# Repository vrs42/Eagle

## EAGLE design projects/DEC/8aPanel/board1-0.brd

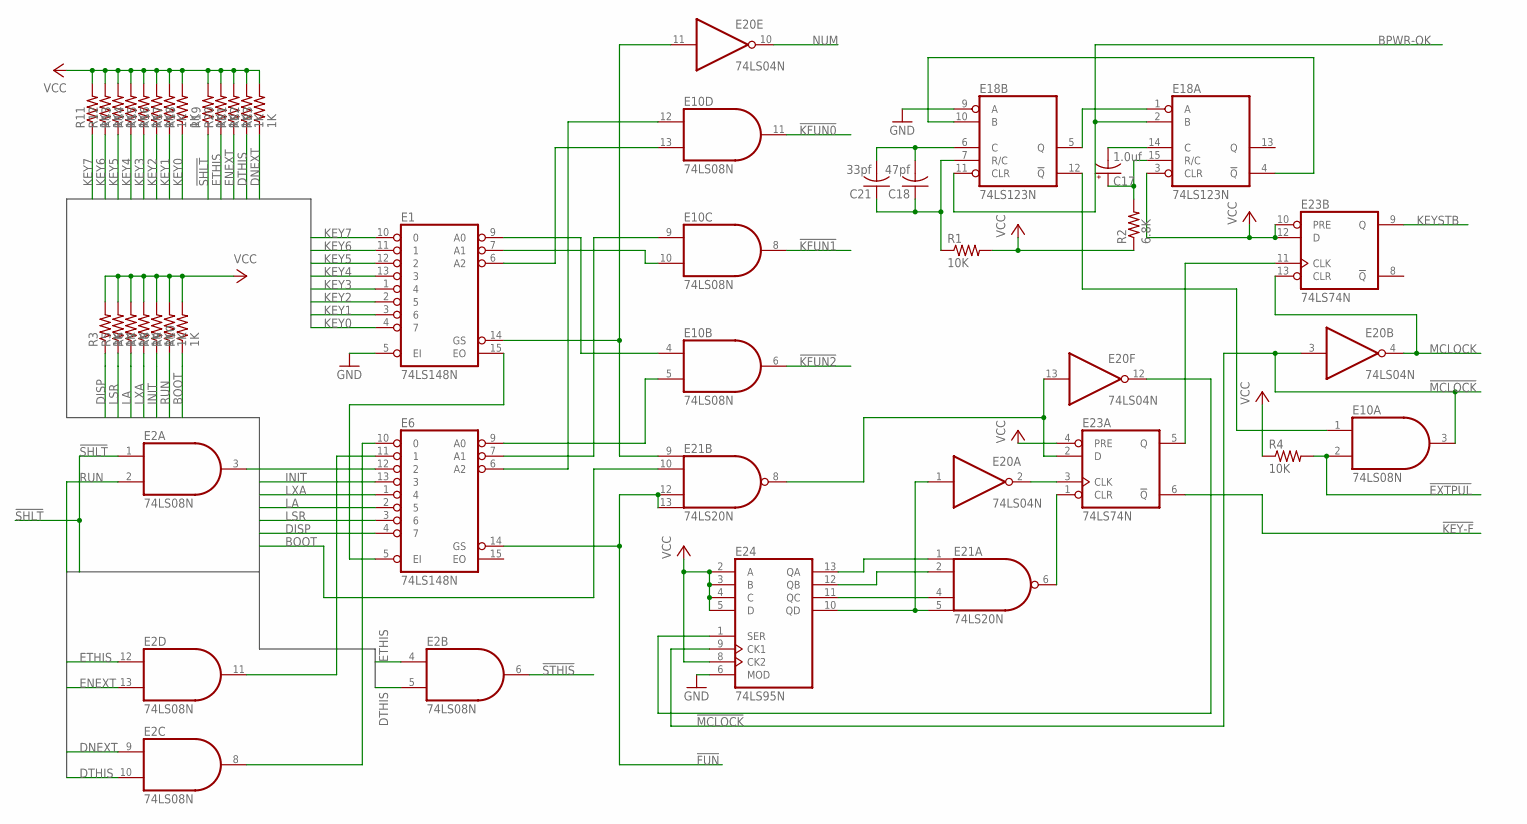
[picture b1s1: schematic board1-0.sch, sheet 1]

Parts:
C17: 1.0uf; E15-5
C18: 47pf; C050-025X075
C21: 33pf; C050-025X075
E1, E6: 74LS148N; DIL16
E2, E10: 74LS08N; DIL14
E18: 74LS123N; DIL16
E20: 74LS04N; DIL14
E21: 74LS20N; DIL14
E23: 74LS74N; DIL14
E24: 74LS95N; DIL14
R1, R4: 10K; 0207/10
R2: 6.8K; 0207/10
R3, R5, R6, R7, R8, R9, R10, R11, R12, R13, R14, R15, R16, R17, R18, R19, R20, R21, R22, R23: 1K; 0207/10

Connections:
!EXTPUL: E10.2 (I1), R4.2; also elsewhere on the board
!FUN: E6.14 (GS), E21.12 (I2), E21.13 (I3); also elsewhere on the board
!KEY-F: E23.6 (!Q); also elsewhere on the board
!KFUN0: E10.11 (O); also elsewhere on the board
!KFUN1: E10.8 (O); also elsewhere on the board
!KFUN2: E10.6 (O); also elsewhere on the board
!MCLOCK: E10.3 (O), E20.3 (I), E24.9 (CK1); also elsewhere on the board
!SHLT: E2.1 (I0), R19.1; also elsewhere on the board
!STHIS: E2.6 (O); also elsewhere on the board
BOOT: E21.10 (I1), R10.1; also elsewhere on the board
BPWR-OK: E18.2 (B), E18.11 (CLR); also elsewhere on the board
DISP: E6.4 (7), R3.1; also elsewhere on the board
DNEXT: E2.9 (I0), R23.1; also elsewhere on the board
DTHIS: E2.5 (I1), E2.10 (I1), R22.1; also elsewhere on the board
ENEXT: E2.13 (I1), R21.1; also elsewhere on the board
ETHIS: E2.4 (I0), E2.12 (I0), R20.1; also elsewhere on the board
GND: E1.5 (EI), E1.8 (GND), E2.7 (GND), E6.8 (GND), E10.7 (GND), E18.8 (GND), E18.9 (A), E20.7 (GND), E21.7 (GND), E23.7 (GND), E24.6 (MOD), E24.7 (GND); also elsewhere on the board
INIT: E6.13 (3), R8.1; also elsewhere on the board
KEY0: E1.4 (7), R18.1; also elsewhere on the board
KEY1: E1.3 (6), R17.1; also elsewhere on the board
KEY2: E1.2 (5), R16.1; also elsewhere on the board
KEY3: E1.1 (4), R15.1; also elsewhere on the board
KEY4: E1.13 (3), R14.1; also elsewhere on the board
KEY5: E1.12 (2), R13.1; also elsewhere on the board
KEY6: E1.11 (1), R12.1; also elsewhere on the board
KEY7: E1.10 (0), R11.1; also elsewhere on the board
KEYSTB: E23.9 (Q); also elsewhere on the board
LA: E6.2 (5), R6.1; also elsewhere on the board
LSR: E6.3 (6), R5.1; also elsewhere on the board
LXA: E6.1 (4), R7.1; also elsewhere on the board
MCLOCK: E20.4 (O), E23.13 (CLR); also elsewhere on the board
unnamed: E1.6 (A2), E10.13 (I1)
unnamed: E1.7 (A1), E10.10 (I1)
unnamed: E1.9 (A0), E10.4 (I0)
unnamed: E1.14 (GS), E20.11 (I), E21.9 (I0)
unnamed: E6.6 (A2), E10.12 (I0)
unnamed: E6.7 (A1), E10.9 (I0)
unnamed: E6.9 (A0), E10.5 (I1)
unnamed: E1.15 (EO), E6.5 (EI)
unnamed: E21.1 (I0), E24.13 (QA)
unnamed: E21.2 (I1), E24.12 (QB)
unnamed: E21.4 (I2), E24.11 (QC)
unnamed: E20.1 (I), E21.5 (I3), E24.10 (QD)
unnamed: E21.6 (O), E23.1 (CLR)
unnamed: E20.2 (O), E23.3 (CLK)
unnamed: E20.13 (I), E21.8 (O), E23.2 (D)
unnamed: E20.12 (O), E24.1 (SER)
unnamed: E23.5 (Q), E23.11 (CLK)
unnamed: E18.1 (A), E18.5 (Q)
unnamed: C18.1, C21.1, E18.7 (R/C), R1.1
unnamed: C17.+, E18.15 (R/C), R2.2
unnamed: C18.2, C21.2, E18.6 (C)
unnamed: C17.-, E18.14 (C)
unnamed: E2.3 (O), E6.12 (2)
unnamed: E18.4 (!Q), E18.10 (B)
unnamed: E2.11 (O), E6.11 (1)
unnamed: E2.8 (O), E6.10 (0)
unnamed: E10.1 (I0), E18.12 (!Q)
NUM: E20.10 (O); also elsewhere on the board
RUN: E2.2 (I1), R9.1; also elsewhere on the board
VCC: E1.16 (VCC), E2.14 (VCC), E6.16 (VCC), E10.14 (VCC), E18.3 (CLR), E18.16 (VCC), E20.14 (VCC), E21.14 (VCC), E23.4 (PRE), E23.10 (PRE), E23.12 (D), E23.14 (VCC), E24.2 (A), E24.3 (B), E24.4 (C), E24.5 (D), E24.8 (CK2), E24.14 (VCC), R1.2, R2.1, R3.2, R4.1, R5.2, R6.2, R7.2, R8.2, R9.2, R10.2, R11.2, R12.2, R13.2, R14.2, R15.2, R16.2, R17.2, R18.2, R19.2, R20.2, R21.2, R22.2, R23.2; also elsewhere on the board

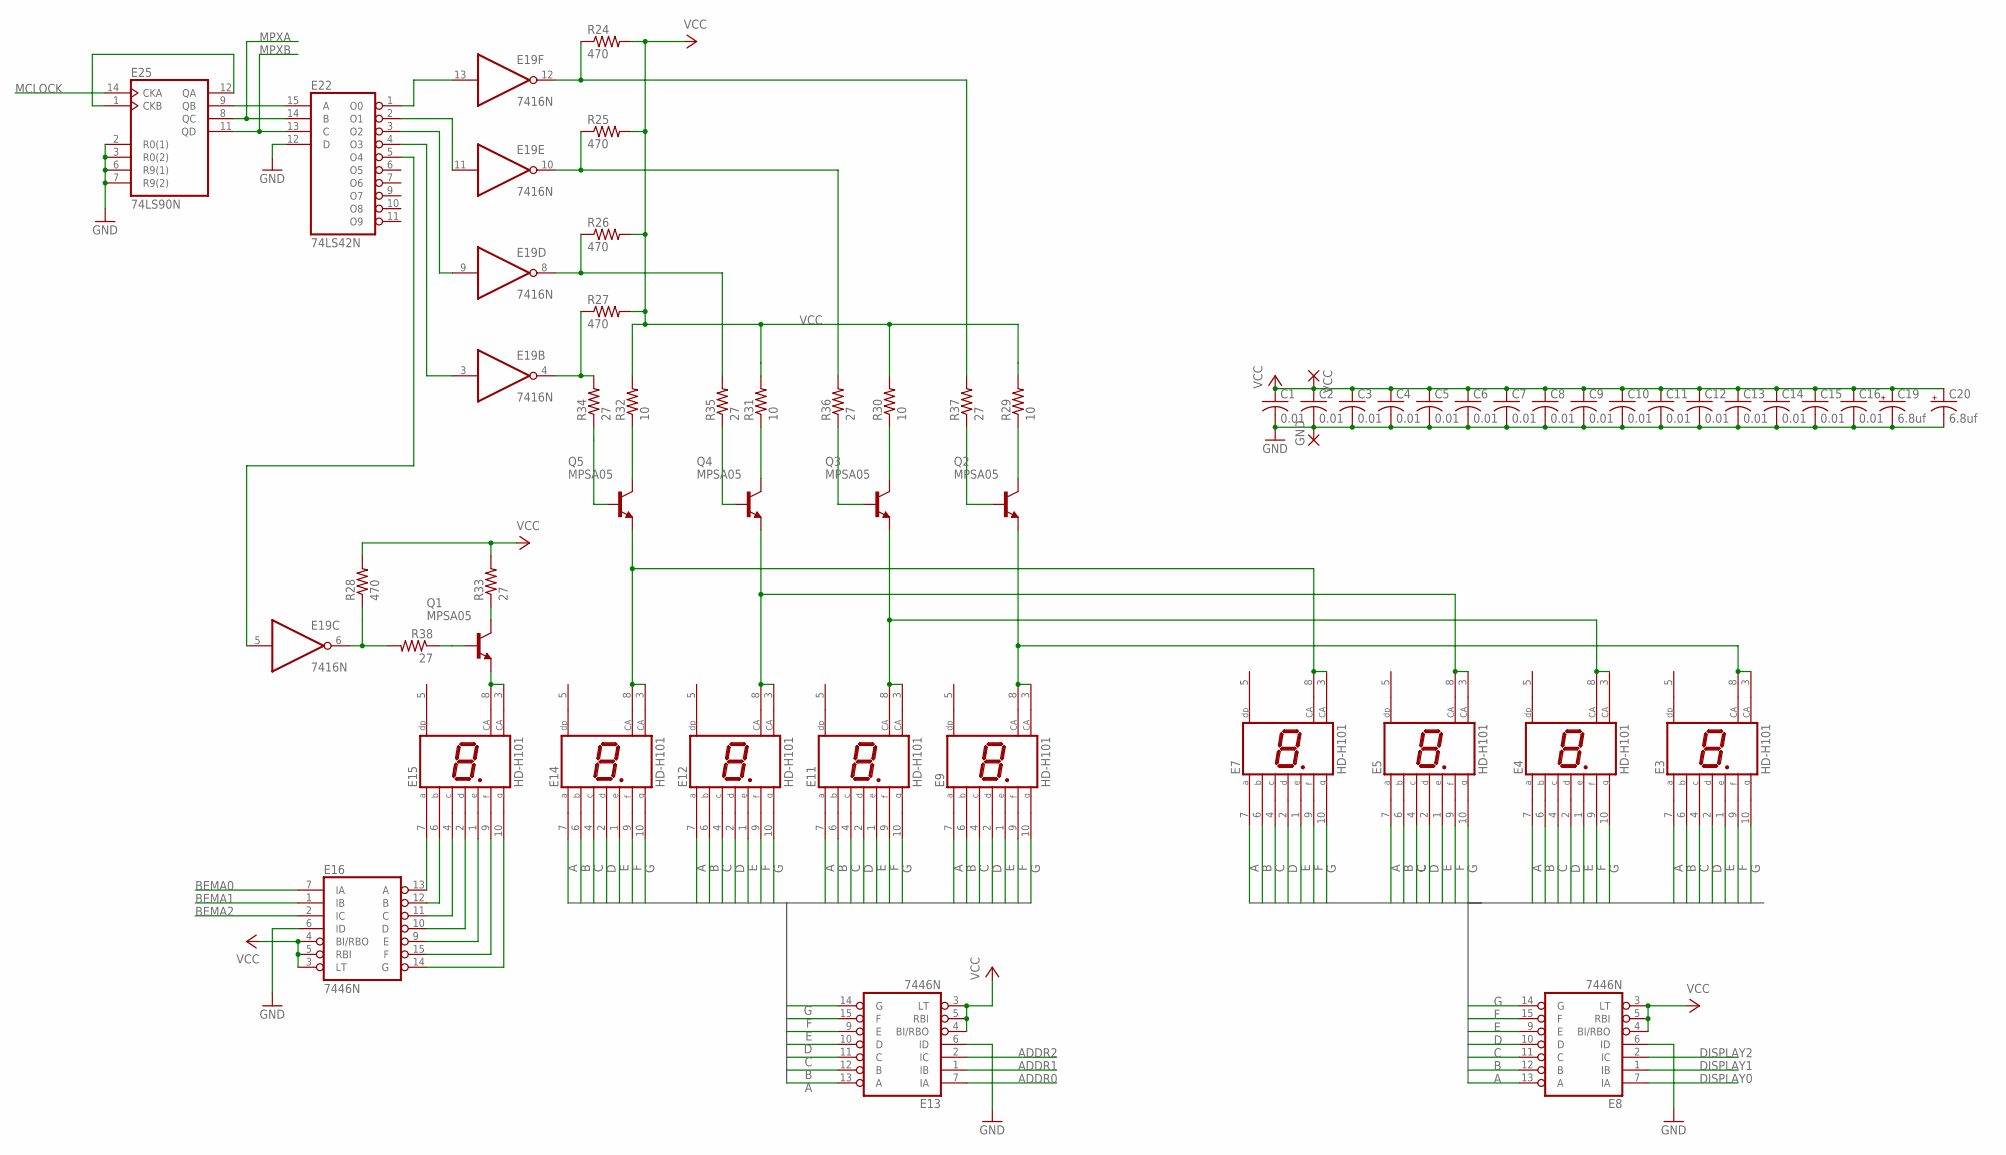
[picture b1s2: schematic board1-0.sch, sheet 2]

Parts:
C1, C2, C3, C4, C5, C6, C7, C8, C9, C10, C11, C12, C13, C14, C15, C16: 0.01; C050-025X075
C19, C20: 6.8uf; E22-6
E3, E4, E5, E7, E9, E11, E12, E14, E15: HD-H101; HDSP-M
E8, E13, E16: 7446N; DIL16
E19: 7416N; DIL14
E22: 74LS42N; DIL16
E25: 74LS90N; DIL14
GND: 3,81/1,4
Q1, Q2, Q3, Q4, Q5: MPSA05; TO18
R24, R25, R26, R27, R28: 470; 0207/10
R29, R30, R31, R32: 10; 0207/10
R33, R34, R35, R36, R37, R38: 27; 0207/10
VCC: 3,81/1,4

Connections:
A: E3.7 (A), E4.7 (A), E5.7 (A), E7.7 (A), E8.13 (A), E9.7 (A), E11.7 (A), E12.7 (A), E13.13 (A), E14.7 (A)
ADDR0: E13.7 (IA); also elsewhere on the board
ADDR1: E13.1 (IB); also elsewhere on the board
ADDR2: E13.2 (IC); also elsewhere on the board
B: E3.6 (B), E4.6 (B), E5.6 (B), E7.6 (B), E8.12 (B), E9.6 (B), E11.6 (B), E12.6 (B), E13.12 (B), E14.6 (B)
BEMA0: E16.7 (IA); also elsewhere on the board
BEMA1: E16.1 (IB); also elsewhere on the board
BEMA2: E16.2 (IC); also elsewhere on the board
C: E3.4 (C), E4.4 (C), E5.4 (C), E7.4 (C), E8.11 (C), E9.4 (C), E11.4 (C), E12.4 (C), E13.11 (C), E14.4 (C)
D: E3.2 (D), E4.2 (D), E5.2 (D), E7.2 (D), E8.10 (D), E9.2 (D), E11.2 (D), E12.2 (D), E13.10 (D), E14.2 (D)
DISPLAY0: E8.7 (IA); also elsewhere on the board
DISPLAY1: E8.1 (IB); also elsewhere on the board
DISPLAY2: E8.2 (IC); also elsewhere on the board
E: E3.1 (E), E4.1 (E), E5.1 (E), E7.1 (E), E8.9 (E), E9.1 (E), E11.1 (E), E12.1 (E), E13.9 (E), E14.1 (E)
F: E3.9 (F), E4.9 (F), E5.9 (F), E7.9 (F), E8.15 (F), E9.9 (F), E11.9 (F), E12.9 (F), E13.15 (F), E14.9 (F)
G: E3.10 (G), E4.10 (G), E5.10 (G), E7.10 (G), E8.14 (G), E9.10 (G), E11.10 (G), E12.10 (G), E13.14 (G), E14.10 (G)
GND: C1.2, C2.2, C3.2, C4.2, C5.2, C6.2, C7.2, C8.2, C9.2, C10.2, C11.2, C12.2, C13.2, C14.2, C15.2, C16.2, C19.-, C20.-, E8.6 (ID), E8.8 (GND), E13.6 (ID), E13.8 (GND), E16.6 (ID), E16.8 (GND), E19.7 (GND), E22.8 (GND), E22.12 (D), E25.2 (R0(1)), E25.3 (R0(2)), E25.6 (R9(1)), E25.7 (R9(2)), E25.10 (GND), GND.1; also elsewhere on the board
MCLOCK: E25.14 (CKA); also elsewhere on the board
MPXA: E22.14 (B), E25.8 (QC); also elsewhere on the board
MPXB: E22.13 (C), E25.11 (QD); also elsewhere on the board
unnamed: E15.7 (A), E16.13 (A)
unnamed: E15.6 (B), E16.12 (B)
unnamed: E15.4 (C), E16.11 (C)
unnamed: E15.2 (D), E16.10 (D)
unnamed: E15.1 (E), E16.9 (E)
unnamed: E15.9 (F), E16.15 (F)
unnamed: E15.10 (G), E16.14 (G)
unnamed: E19.12 (O), R24.1, R37.2
unnamed: E19.10 (O), R25.1, R36.2
unnamed: E22.15 (A), E25.9 (QB)
unnamed: E25.1 (CKB), E25.12 (QA)
unnamed: E19.8 (O), R26.1, R35.2
unnamed: E19.13 (I), E22.1 (O0)
unnamed: E19.11 (I), E22.2 (O1)
unnamed: E19.9 (I), E22.3 (O2)
unnamed: E19.3 (I), E22.4 (O3)
unnamed: E19.5 (I), E22.5 (O4)
unnamed: E19.4 (O), R27.1, R34.2
unnamed: E15.3 (CA), E15.8 (CA), Q1.1 (E)
unnamed: Q2.3 (C), R29.1
unnamed: Q3.3 (C), R30.1
unnamed: Q4.3 (C), R31.1
unnamed: Q5.3 (C), R32.1
unnamed: Q1.3 (C), R33.1
unnamed: Q1.2 (B), R38.1
unnamed: E7.3 (CA), E7.8 (CA), E14.3 (CA), E14.8 (CA), Q5.1 (E)
unnamed: Q5.2 (B), R34.1
unnamed: Q4.2 (B), R35.1
unnamed: Q3.2 (B), R36.1
unnamed: Q2.2 (B), R37.1
unnamed: E19.6 (O), R28.1, R38.2
unnamed: E5.3 (CA), E5.8 (CA), E12.3 (CA), E12.8 (CA), Q4.1 (E)
unnamed: E4.3 (CA), E4.8 (CA), E11.3 (CA), E11.8 (CA), Q3.1 (E)
unnamed: E3.3 (CA), E3.8 (CA), E9.3 (CA), E9.8 (CA), Q2.1 (E)
VCC: C1.1, C2.1, C3.1, C4.1, C5.1, C6.1, C7.1, C8.1, C9.1, C10.1, C11.1, C12.1, C13.1, C14.1, C15.1, C16.1, C19.+, C20.+, E8.3 (LT), E8.4 (BI/RBO), E8.5 (RBI), E8.16 (VCC), E13.3 (LT), E13.4 (BI/RBO), E13.5 (RBI), E13.16 (VCC), E16.3 (LT), E16.4 (BI/RBO), E16.5 (RBI), E16.16 (VCC), E19.14 (VCC), E22.16 (VCC), E25.5 (VCC), R24.2, R25.2, R26.2, R27.2, R28.2, R29.2, R30.2, R31.2, R32.2, R33.2, VCC.1; also elsewhere on the board

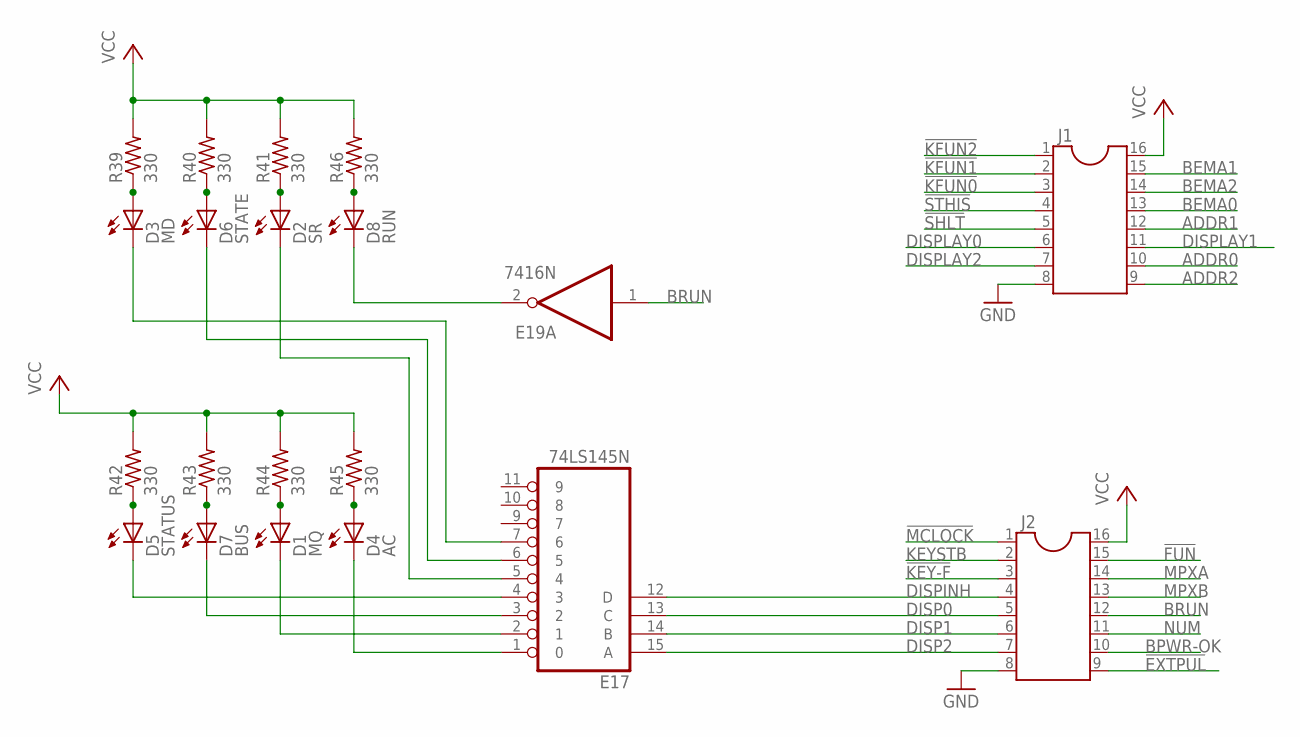
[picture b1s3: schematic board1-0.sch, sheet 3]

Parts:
D1: MQ; LED5MM
D2: SR; LED5MM
D3: MD; LED5MM
D4: AC; LED5MM
D5: STATUS; LED5MM
D6: STATE; LED5MM
D7: BUS; LED5MM
D8: RUN; LED5MM
E17: 74LS145N; DIL16
E19: 7416N; DIL14
J1, J2: DIL16S; SOCKET-16
R39, R40, R41, R42, R43, R44, R45, R46: 330; 0207/10

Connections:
!EXTPUL: J2.9; also elsewhere on the board
!FUN: J2.15; also elsewhere on the board
!KEY-F: J2.3; also elsewhere on the board
!KFUN0: J1.3; also elsewhere on the board
!KFUN1: J1.2; also elsewhere on the board
!KFUN2: J1.1; also elsewhere on the board
!MCLOCK: J2.1; also elsewhere on the board
!SHLT: J1.5; also elsewhere on the board
!STHIS: J1.4; also elsewhere on the board
ADDR0: J1.10; also elsewhere on the board
ADDR1: J1.12; also elsewhere on the board
ADDR2: J1.9; also elsewhere on the board
BEMA0: J1.13; also elsewhere on the board
BEMA1: J1.15; also elsewhere on the board
BEMA2: J1.14; also elsewhere on the board
BPWR-OK: J2.10; also elsewhere on the board
BRUN: E19.1 (I), J2.12
DISP0: E17.13 (C), J2.5
DISP1: E17.14 (B), J2.6
DISP2: E17.15 (A), J2.7
DISPINH: E17.12 (D), J2.4
DISPLAY0: J1.6; also elsewhere on the board
DISPLAY1: J1.11; also elsewhere on the board
DISPLAY2: J1.7; also elsewhere on the board
GND: E17.8 (GND), E19.7 (GND), J1.8, J2.8; also elsewhere on the board
KEYSTB: J2.2; also elsewhere on the board
MPXA: J2.14; also elsewhere on the board
MPXB: J2.13; also elsewhere on the board
unnamed: D3.A, R39.1
unnamed: D6.A, R40.1
unnamed: D2.A, R41.1
unnamed: D5.A, R42.1
unnamed: D7.A, R43.1
unnamed: D1.A, R44.1
unnamed: D4.A, R45.1
unnamed: D8.A, R46.1
unnamed: D8.K (C), E19.2 (O)
unnamed: D4.K (C), E17.1 (0)
unnamed: D1.K (C), E17.2 (1)
unnamed: D7.K (C), E17.3 (2)
unnamed: D5.K (C), E17.4 (3)
unnamed: D2.K (C), E17.5 (4)
unnamed: D6.K (C), E17.6 (5)
unnamed: D3.K (C), E17.7 (6)
NUM: J2.11; also elsewhere on the board
VCC: E17.16 (VCC), E19.14 (VCC), J1.16, J2.16, R39.2, R40.2, R41.2, R42.2, R43.2, R44.2, R45.2, R46.2; also elsewhere on the board

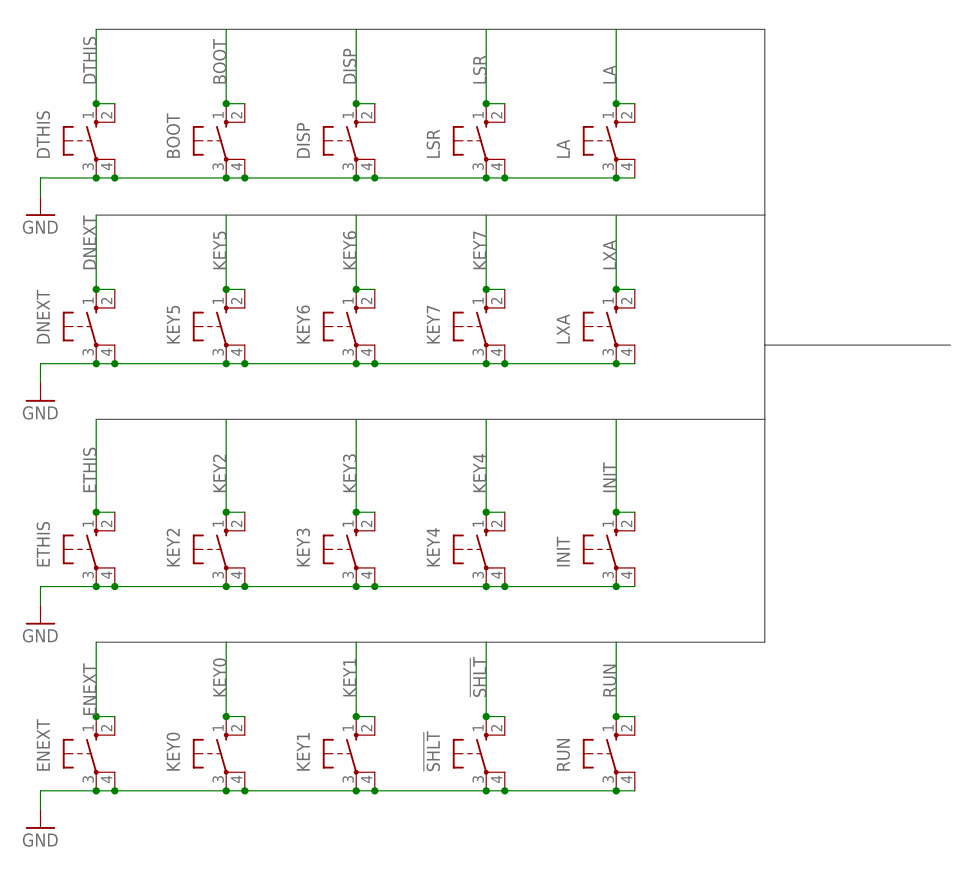
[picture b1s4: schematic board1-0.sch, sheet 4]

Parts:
!SHLT: 40-XX; B3F-40XX
BOOT: 40-XX; B3F-40XX
DISP: 40-XX; B3F-40XX
DNEXT: 40-XX; B3F-40XX
DTHIS: 40-XX; B3F-40XX
ENEXT: 40-XX; B3F-40XX
ETHIS: 40-XX; B3F-40XX
INIT: 40-XX; B3F-40XX
KEY0, KEY1, KEY2, KEY3, KEY4, KEY5, KEY6, KEY7: 40-XX; B3F-40XX
LA: 40-XX; B3F-40XX
LSR: 40-XX; B3F-40XX
LXA: 40-XX; B3F-40XX
RUN: 40-XX; B3F-40XX

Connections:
!SHLT: !SHLT.1 (S), !SHLT.2 (S1); also elsewhere on the board
BOOT: BOOT.1 (S), BOOT.2 (S1); also elsewhere on the board
DISP: DISP.1 (S), DISP.2 (S1); also elsewhere on the board
DNEXT: DNEXT.1 (S), DNEXT.2 (S1); also elsewhere on the board
DTHIS: DTHIS.1 (S), DTHIS.2 (S1); also elsewhere on the board
ENEXT: ENEXT.1 (S), ENEXT.2 (S1); also elsewhere on the board
ETHIS: ETHIS.1 (S), ETHIS.2 (S1); also elsewhere on the board
GND: !SHLT.3, !SHLT.4 (P1), BOOT.3, BOOT.4 (P1), DISP.3, DISP.4 (P1), DNEXT.3, DNEXT.4 (P1), DTHIS.3, DTHIS.4 (P1), ENEXT.3, ENEXT.4 (P1), ETHIS.3, ETHIS.4 (P1), INIT.3, INIT.4 (P1), KEY0.3, KEY0.4 (P1), KEY1.3, KEY1.4 (P1), KEY2.3, KEY2.4 (P1), KEY3.3, KEY3.4 (P1), KEY4.3, KEY4.4 (P1), KEY5.3, KEY5.4 (P1), KEY6.3, KEY6.4 (P1), KEY7.3, KEY7.4 (P1), LA.3, LA.4 (P1), LSR.3, LSR.4 (P1), LXA.3, LXA.4 (P1), RUN.3, RUN.4 (P1); also elsewhere on the board
INIT: INIT.1 (S), INIT.2 (S1); also elsewhere on the board
KEY0: KEY0.1 (S), KEY0.2 (S1); also elsewhere on the board
KEY1: KEY1.1 (S), KEY1.2 (S1); also elsewhere on the board
KEY2: KEY2.1 (S), KEY2.2 (S1); also elsewhere on the board
KEY3: KEY3.1 (S), KEY3.2 (S1); also elsewhere on the board
KEY4: KEY4.1 (S), KEY4.2 (S1); also elsewhere on the board
KEY5: KEY5.1 (S), KEY5.2 (S1); also elsewhere on the board
KEY6: KEY6.1 (S), KEY6.2 (S1); also elsewhere on the board
KEY7: KEY7.1 (S), KEY7.2 (S1); also elsewhere on the board
LA: LA.1 (S), LA.2 (S1); also elsewhere on the board
LSR: LSR.1 (S), LSR.2 (S1); also elsewhere on the board
LXA: LXA.1 (S), LXA.2 (S1); also elsewhere on the board
RUN: RUN.1 (S), RUN.2 (S1); also elsewhere on the board

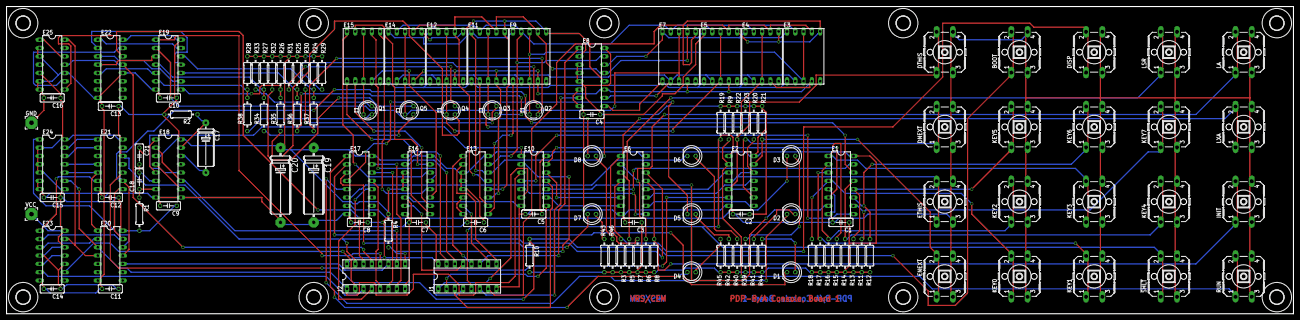
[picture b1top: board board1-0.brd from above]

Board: 4 copper layers, 393.7 x 94.0 mm, 139 parts (0 on the bottom side), 134 nets.

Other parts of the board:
U$2, U$11, U$12, U$13, U$14, U$15, U$16, U$17, U$18, U$19: 4,3

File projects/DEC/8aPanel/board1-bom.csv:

Qty,Value,Device,Package,Parts,Description
2,,"3,81/1,4","3,81/1,4","GND, VCC",THROUGH-HOLE PAD
20,,40-XX,B3F-40XX,"!SHLT, BOOT, DISP, DNEXT, DTHIS, ENEXT, ETHIS, INIT, KEY0, KEY1, KEY2, KEY3, KEY4, KEY5, KEY6, KEY7, LA, LSR, LXA, RUN",OMRON SWITCH
2,,DIL16S,SOCKET-16,"J1, J2",Dual In Line / Socket
16,0.01,C-US050-025X075,C050-025X075,"C1, C2, C3, C4, C5, C6, C7, C8, C9, C10, C11, C12, C13, C14, C15, C16","CAPACITOR, American symbol"
1,1.0uf,CPOL-USE15-5AXIAL,E15-5,C17,"POLARIZED CAPACITOR, American symbol"
4,10,R-US_0207/10,0207/10,"R29, R30, R31, R32","RESISTOR, American symbol"
2,10K,R-US_0207/10,0207/10,"R1, R4","RESISTOR, American symbol"
20,1K,R-US_0207/10,0207/10,"R3, R5, R6, R7, R8, R9, R10, R11, R12, R13, R14, R15, R16, R17, R18, R19, R20, R21, R22, R23","RESISTOR, American symbol"
1,220uf,CPOL-USE22-6AXIAL,E22-6,C19,"POLARIZED CAPACITOR, American symbol"
6,27,R-US_0207/10,0207/10,"R33, R34, R35, R36, R37, R38","RESISTOR, American symbol"
8,330,R-US_0207/10,0207/10,"R39, R40, R41, R42, R43, R44, R45, R46","RESISTOR, American symbol"
1,33pf,C-US050-025X075,C050-025X075,C21,"CAPACITOR, American symbol"
5,470,R-US_0207/10,0207/10,"R24, R25, R26, R27, R28","RESISTOR, American symbol"
1,47pf,C-US050-025X075,C050-025X075,C18,"CAPACITOR, American symbol"
1,6.8K,R-US_0207/10,0207/10,R2,"RESISTOR, American symbol"
1,6.8uf,CPOL-USE22-6AXIAL,E22-6,C20,"POLARIZED CAPACITOR, American symbol"
1,7416N,7416N,DIL14,E19,"Hex INVERTER, open collector, high-voltage"
3,7446N,7446N,DIL16,"E8, E13, E16","BCD to seven segment DECODER/DRIVER, open collector"
1,74LS04N,74LS04N,DIL14,E20,Hex INVERTER
2,74LS08N,74LS08N,DIL14,"E2, E10",Quad 2-input AND gate
1,74LS123N,74LS123N,DIL16,E18,Retriggerable monostable MULTIVIBRATOR
1,74LS145N,74LS145N,DIL16,E17,BCD to decimal DECODER/DRIVER
2,74LS148N,74LS148N,DIL16,"E1, E6",10-line to 4-line and 8-line to 3-line PRIORITY ENCODER
1,74LS20N,74LS20N,DIL14,E21,Dual 4-input NAND gate
1,74LS42N,74LS42N,DIL16,E22,4-line to 10-line DECODER (1-of-10)
1,74LS74N,74LS74N,DIL14,E23,"Dual D type positive edge triggered FLIP FLOP, preset and clear"
1,74LS90N,74LS90N,DIL14,E25,"Decade, divide by twelve and binary COUNTER"
1,74LS95N,74LS95N,DIL14,E24,4-bit parallel access SHIFT REGISTER
1,AC,LED5MM,LED5MM,D4,LED
1,BUS,LED5MM,LED5MM,D7,LED
9,HD-H101,HD-H101,HDSP-M,"E3, E4, E5, E7, E9, E11, E12, E14, E15",LED DISPLAY
1,MD,LED5MM,LED5MM,D3,LED
5,MPSA05,2N2222A,TO18,"Q1, Q2, Q3, Q4, Q5",NPN Transistor
1,MQ,LED5MM,LED5MM,D1,LED
1,RUN,LED5MM,LED5MM,D8,LED
1,SR,LED5MM,LED5MM,D2,LED
1,STATE,LED5MM,LED5MM,D6,LED
1,STATUS,LED5MM,LED5MM,D5,LED

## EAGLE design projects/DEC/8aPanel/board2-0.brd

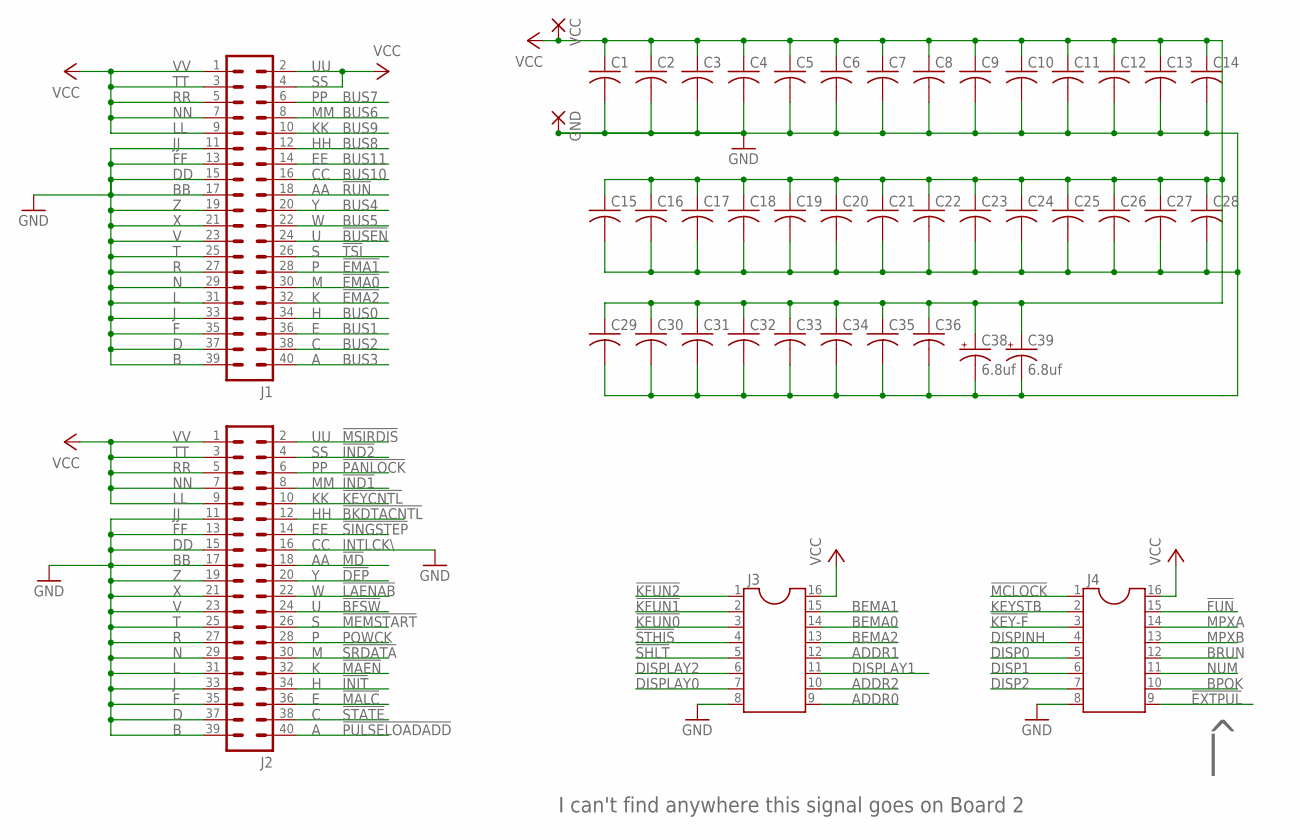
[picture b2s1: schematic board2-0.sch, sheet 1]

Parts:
C1, C2, C3, C4, C5, C6, C7, C8, C9, C10, C11, C12, C13, C14, C15, C16, C17, C18, C19, C20, C21, C22, C23, C24, C25, C26, C27, C28, C29, C30, C31, C32, C33, C34, C35, C36: C-US050-025X075; C050-025X075
C38, C39: 6.8uf; E15-5
GND: 3,81/1,4
J1, J2: 40H
J3, J4: DIL16S; SOCKET-16
VCC: 3,81/1,4

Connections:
!BFSW: J2.24; also elsewhere on the board
!BKDTACNTL: J2.12; also elsewhere on the board
!BUSEN: J1.24; also elsewhere on the board
!DEP: J2.20; also elsewhere on the board
!EMA0: J1.30; also elsewhere on the board
!EMA1: J1.28; also elsewhere on the board
!EMA2: J1.32; also elsewhere on the board
!EXTPUL: J4.9
!FUN: J4.15; also elsewhere on the board
!IND1: J2.8; also elsewhere on the board
!IND2: J2.4; also elsewhere on the board
!INIT: J2.34; also elsewhere on the board
!KEY-F: J4.3; also elsewhere on the board
!KEYCNTL: J2.10; also elsewhere on the board
!KFUN0: J3.3; also elsewhere on the board
!KFUN1: J3.2; also elsewhere on the board
!KFUN2: J3.1; also elsewhere on the board
!LAENAB: J2.22; also elsewhere on the board
!MAEN: J2.32; also elsewhere on the board
!MALC: J2.36; also elsewhere on the board
!MCLOCK: J4.1; also elsewhere on the board
!MD: J2.18; also elsewhere on the board
!MEMSTART: J2.26; also elsewhere on the board
!MSIRDIS: J2.2; also elsewhere on the board
!PANLOCK: J2.6; also elsewhere on the board
!PULSELOADADD: J2.40; also elsewhere on the board
!RUN: J1.18; also elsewhere on the board
!SHLT: J3.5; also elsewhere on the board
!SINGSTEP: J2.14; also elsewhere on the board
!SRDATA: J2.30; also elsewhere on the board
!STATE: J2.38; also elsewhere on the board
!STHIS: J3.4; also elsewhere on the board
!TSI: J1.26; also elsewhere on the board
ADDR0: J3.9; also elsewhere on the board
ADDR1: J3.12; also elsewhere on the board
ADDR2: J3.10; also elsewhere on the board
BEMA0: J3.14; also elsewhere on the board
BEMA1: J3.15; also elsewhere on the board
BEMA2: J3.13; also elsewhere on the board
BPOK: J4.10; also elsewhere on the board
BRUN: J4.12; also elsewhere on the board
BUS0: J1.34; also elsewhere on the board
BUS1: J1.36; also elsewhere on the board
BUS2: J1.38; also elsewhere on the board
BUS3: J1.40; also elsewhere on the board
BUS4: J1.20; also elsewhere on the board
BUS5: J1.22; also elsewhere on the board
BUS6: J1.8; also elsewhere on the board
BUS7: J1.6; also elsewhere on the board
BUS8: J1.12; also elsewhere on the board
BUS9: J1.10; also elsewhere on the board
BUS10: J1.16; also elsewhere on the board
BUS11: J1.14; also elsewhere on the board
DISP0: J4.5; also elsewhere on the board
DISP1: J4.6; also elsewhere on the board
DISP2: J4.7; also elsewhere on the board
DISPINH: J4.4; also elsewhere on the board
DISPLAY0: J3.7; also elsewhere on the board
DISPLAY1: J3.11; also elsewhere on the board
DISPLAY2: J3.6; also elsewhere on the board
GND: C1.2, C2.2, C3.2, C4.2, C5.2, C6.2, C7.2, C8.2, C9.2, C10.2, C11.2, C12.2, C13.2, C14.2, C15.2, C16.2, C17.2, C18.2, C19.2, C20.2, C21.2, C22.2, C23.2, C24.2, C25.2, C26.2, C27.2, C28.2, C29.2, C30.2, C31.2, C32.2, C33.2, C34.2, C35.2, C36.2, C38.-, C39.-, GND.1, J1.11, J1.13, J1.15, J1.17, J1.19, J1.21, J1.23, J1.25, J1.27, J1.29, J1.31, J1.33, J1.35, J1.37, J1.39, J2.11, J2.13, J2.15, J2.16, J2.17, J2.19, J2.21, J2.23, J2.25, J2.27, J2.29, J2.31, J2.33, J2.35, J2.37, J2.39, J3.8, J4.8; also elsewhere on the board
KEYSTB: J4.2; also elsewhere on the board
MPXA: J4.14; also elsewhere on the board
MPXB: J4.13; also elsewhere on the board
NUM: J4.11; also elsewhere on the board
POWCK: J2.28; also elsewhere on the board
VCC: C1.1, C2.1, C3.1, C4.1, C5.1, C6.1, C7.1, C8.1, C9.1, C10.1, C11.1, C12.1, C13.1, C14.1, C15.1, C16.1, C17.1, C18.1, C19.1, C20.1, C21.1, C22.1, C23.1, C24.1, C25.1, C26.1, C27.1, C28.1, C29.1, C30.1, C31.1, C32.1, C33.1, C34.1, C35.1, C36.1, C38.+, C39.+, J1.1, J1.2, J1.3, J1.4, J1.5, J1.7, J1.9, J2.1, J2.3, J2.5, J2.7, J2.9, J3.16, J4.16, VCC.1; also elsewhere on the board

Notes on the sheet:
INTLCK\\
I can't find anywhere this signal goes on Board 2
